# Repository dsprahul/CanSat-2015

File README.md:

# CanSat-2015
- RaspberryPi A+ Shield with all required sensors for CanSat Competition - 2015 (Sensor Module)
- A boost converter which powers off a 3.7V Li-Ion battery to power various pheripherals of CanSat (Power Module)

# Quick views
## Sensor module schematic

## Sensor module brd top

## Sensor module brd bottom

## Power module brd schematic

## Power module brd top

## Power module brd bottom

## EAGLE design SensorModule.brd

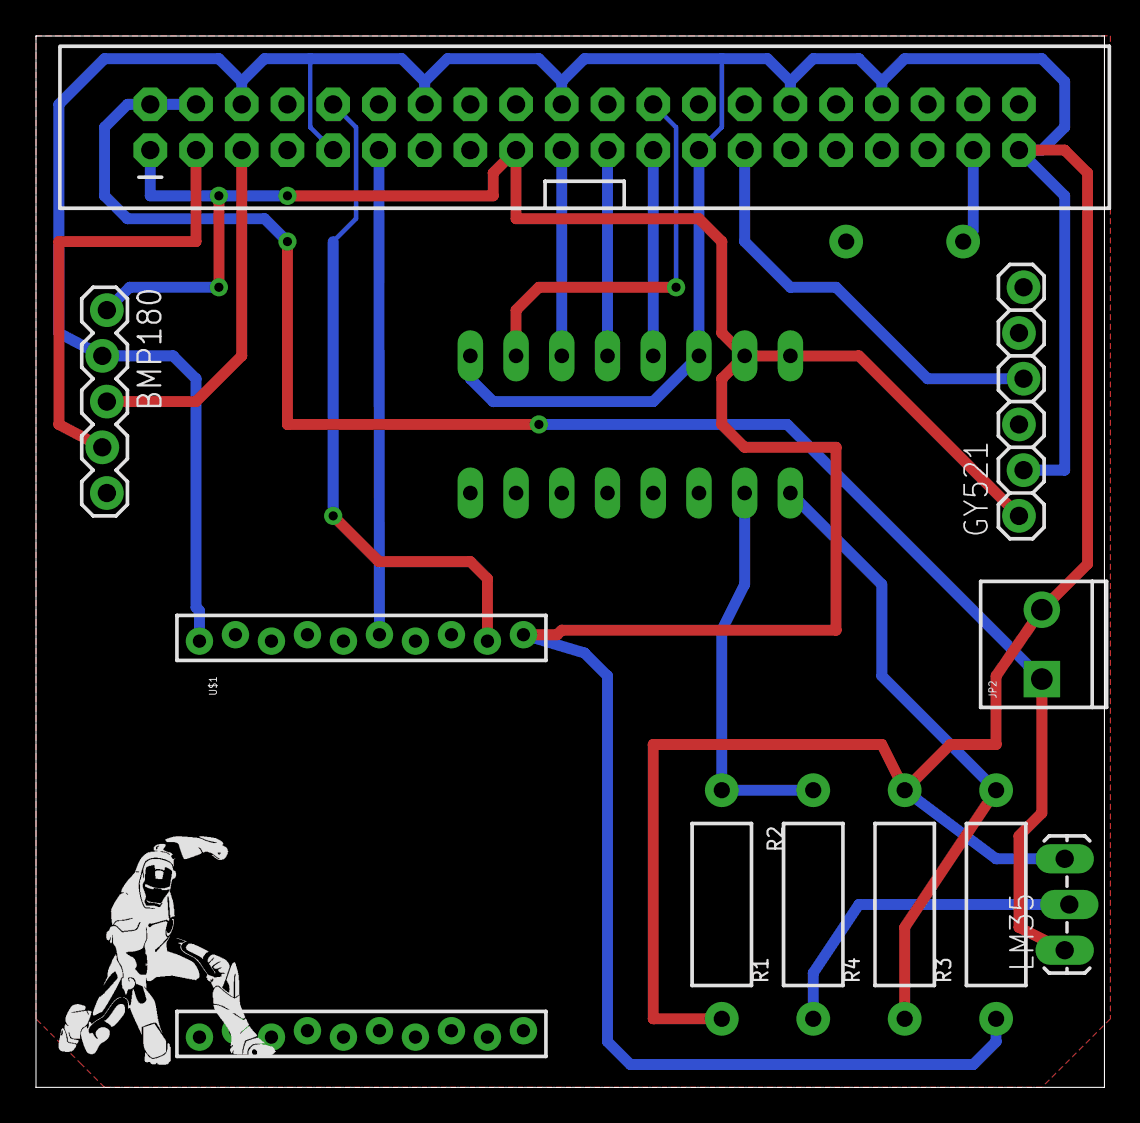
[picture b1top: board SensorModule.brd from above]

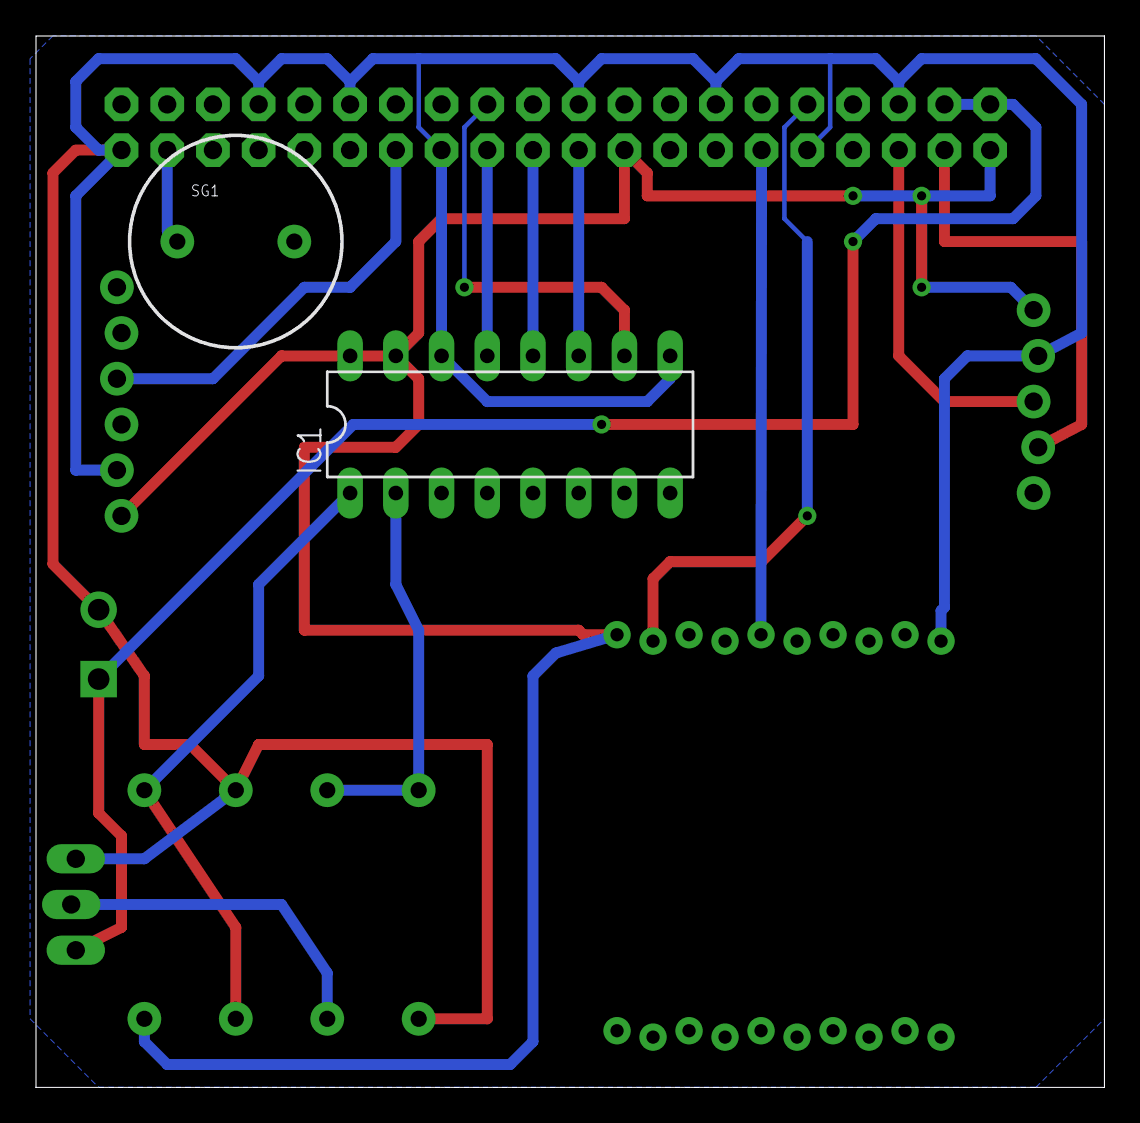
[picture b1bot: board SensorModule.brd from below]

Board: 2 copper layers, 59.4 x 58.4 mm, 12 parts (2 on the bottom side), 16 nets.

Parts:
BMP180: 1X05_LOCK
GY521: 1X06_LOCK
IC1: MCP3008; DIL16
JP1: RASPBERRYPI-B+-GPIO; 2X20-SHROUDED
JP2: SCREWTERMINAL-3.5MM-2_LOCK
LM35: 1X03_LOCK_LONGPADS
R1, R2, R3, R4: AXIAL-0.5
SG1: BUZZERPTH-KIT; BUZZER-12MM-KIT
U$1: XBEE-2XBEE-1_LOCK; XBEE-1_LOCK

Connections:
BUZZ: JP1.37, SG1.-
CLK: IC1.13, JP1.23
CS: IC1.10, JP1.24
GND: BMP180.2, GY521.2, IC1.9, IC1.14, JP1.6, JP1.9, JP1.14, JP1.20, JP1.25, JP1.30, JP1.34, JP1.39, JP2.2, LM35.3, R2.P$2, R4.P$2, SG1.+, U$1.10
MISO: IC1.12, JP1.21
MOSI: IC1.11, JP1.19
NORMTEMP: IC1.2, R1.P$2, R2.P$1
NORMVOLT: IC1.1, R3.P$2, R4.P$1
RST: JP1.11, U$1.5
SCL0: BMP180.3, JP1.5
SDA0: BMP180.4, JP1.3
SDA1: GY521.4, JP1.27
TOUT: LM35.2, R1.P$1
TX: JP1.10, U$1.2
VCC: BMP180.1, GY521.1, IC1.15, IC1.16, JP1.1, JP1.17, R3.P$1, U$1.1
VIN: JP1.2, JP1.4, JP2.1, LM35.1

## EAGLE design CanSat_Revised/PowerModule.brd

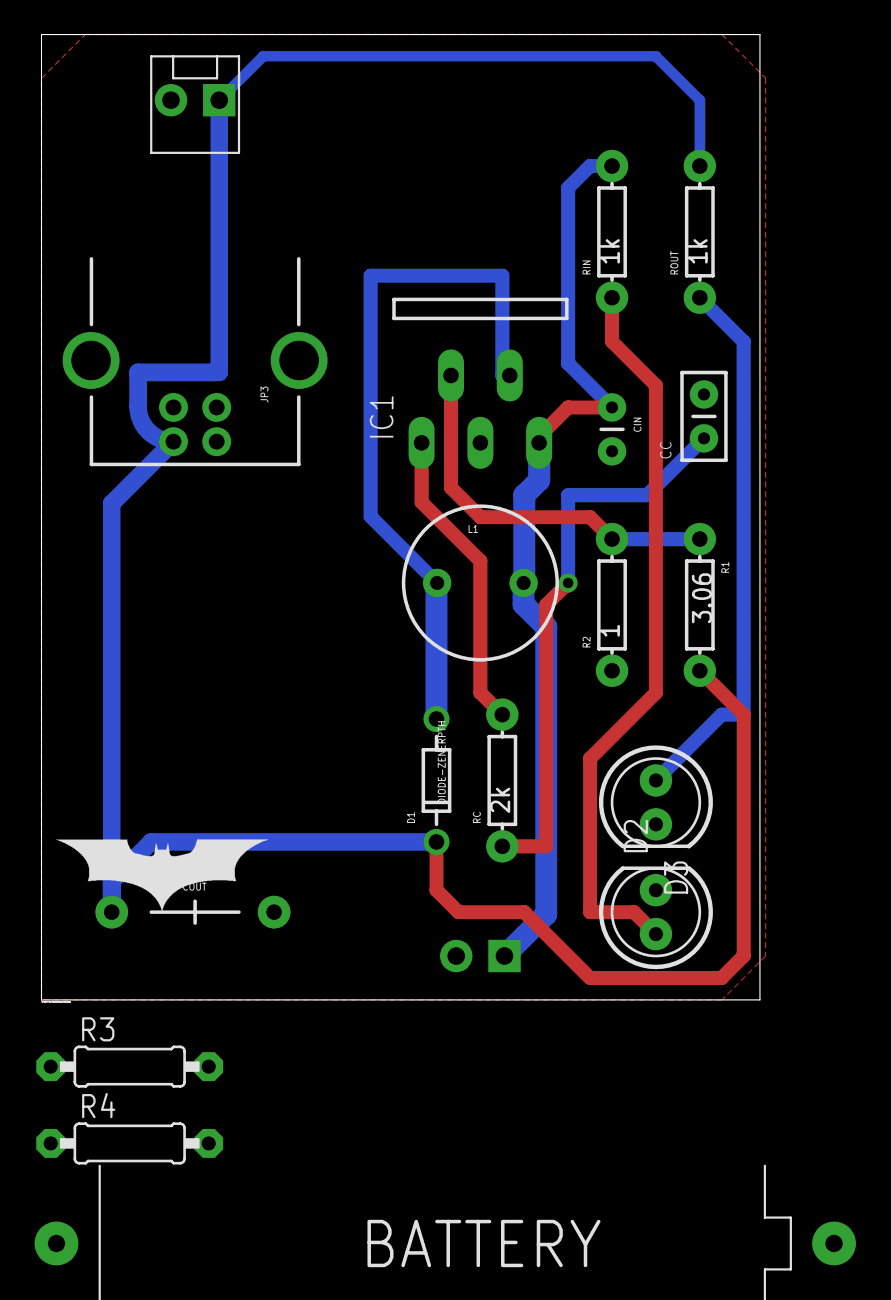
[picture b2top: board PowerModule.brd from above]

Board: 2 copper layers, 41.6 x 55.9 mm, 19 parts (1 on the bottom side), 12 nets.

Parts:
BATTERY: 4.1V ~ 3.7V; 12BH412
CC: 0.5uF; CAP-PTH-SMALLEZ
CIN: 0.1uF; CAP-PTH-SMALL
COUT: 4700uF; CAP-PTH-LARGE
D1: DIODE-ZENERPTH; DIODE-ZENER
D2, D3: LED5MM-KIT
IC1: LM2577T; TO220-5
INPUT: MOLEX-1X2_LOCK
JP3: USB-B; USB-B-PTH
L1: 47uH; RLB0912
OUTPUT: MOLEX-1X2_LOCK
R1: 3.06; AXIAL-0.3EZ
R2: 1; AXIAL-0.3EZ
R3: 1K; 0207/9
R4: 2K; 0207/9
RC: 2k; AXIAL-0.3EZ
RIN: 1k; AXIAL-0.3EZ
ROUT: 1k; AXIAL-0.3EZ

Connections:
COMP: IC1.1, RC.P$2
FB: IC1.2, R1.P$1, R2.P$2
GND: CC.2, CIN.2, COUT.2, D2.K, D3.K, IC1.3, INPUT.2, JP3.GND, OUTPUT.2, R2.P$1
GND-ISO: BATTERY.+, R4.1
unnamed: CC.1, RC.P$1
unnamed: D2.A, RIN.P$1
unnamed: D3.A, ROUT.P$1
unnamed: BATTERY.-, R3.2
SWITCH: D1.P$2, IC1.4, L1.2
TO-ADC: R3.1, R4.2
VIN: CIN.1, IC1.5, INPUT.1, L1.1, RIN.P$2
VOUT: COUT.1, D1.P$1, JP3.VBUS, OUTPUT.1, R1.P$2, ROUT.P$2

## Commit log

2016-02-05 :circus_tent: Added .gitattributes & .gitignore files
2016-02-05 Content merged
    Download SensorModule.sch & PowerModule.sch
2017-03-25 Cleaned Repo
2017-03-25 cleaning repo
2017-03-25 Images for README

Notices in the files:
parts and their libraries:
SparkFun-Capacitors: Licensing: Creative Commons ShareAlike 4.0 International - https://creativecommons.org/licenses/by-sa/4.0
